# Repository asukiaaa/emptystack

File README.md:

# EmptyStack
A kicad project of empty stacking board.

In combination with [ESP32Stack](https://github.com/asukiaaa/esp32stack).

# License
MIT

# References
- [ESP32Stack](https://github.com/asukiaaa/esp32stack)

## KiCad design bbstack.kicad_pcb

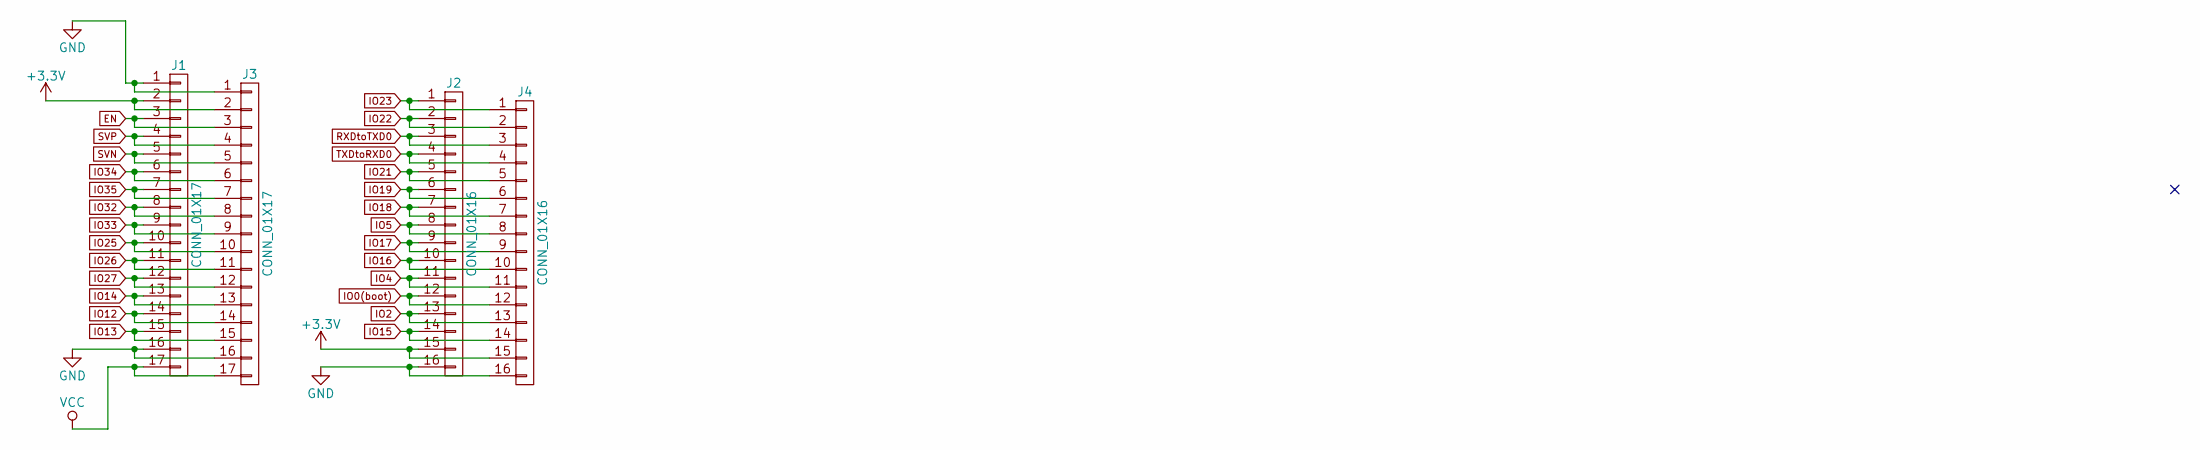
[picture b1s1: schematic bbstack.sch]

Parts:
J1, J3: CONN_01X17; Pin_Header_Straight_1x17_Pitch2.54mm
J2, J4: CONN_01X16; Pin_Header_Straight_1x16_Pitch2.54mm

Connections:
+3V3: J1.2, J2.15, J3.2, J4.15
EN: J1.3, J3.3
GND: J1.1, J1.16, J2.16, J3.1, J3.16, J4.16
IO0(boot): J2.12, J4.12
IO2: J2.13, J4.13
IO4: J2.11, J4.11
IO5: J2.8, J4.8
IO12: J1.14, J3.14
IO13: J1.15, J3.15
IO14: J1.13, J3.13
IO15: J2.14, J4.14
IO16: J2.10, J4.10
IO17: J2.9, J4.9
IO18: J2.7, J4.7
IO19: J2.6, J4.6
IO21: J2.5, J4.5
IO22: J2.2, J4.2
IO23: J2.1, J4.1
IO25: J1.10, J3.10
IO26: J1.11, J3.11
IO27: J1.12, J3.12
IO32: J1.8, J3.8
IO33: J1.9, J3.9
IO34: J1.6, J3.6
IO35: J1.7, J3.7
RXDtoTXD0: J2.3, J4.3
SVN: J1.5, J3.5
SVP: J1.4, J3.4
TXDtoRXD0: J2.4, J4.4
VCC: J1.17, J3.17

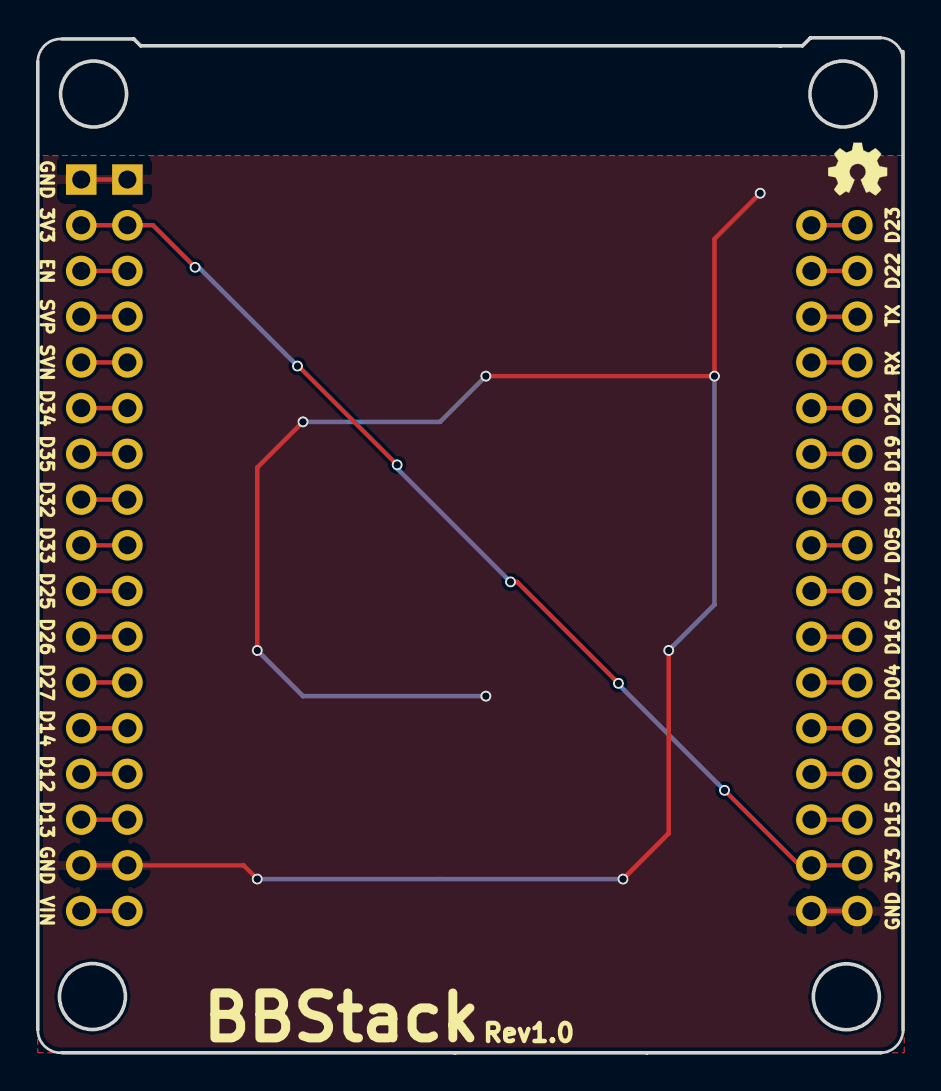
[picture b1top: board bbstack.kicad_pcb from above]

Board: 2 copper layers, 48.1 x 56.4 mm, 4 parts (0 on the bottom side), 30 nets.

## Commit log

2017-04-20 Initial commit bbstack rev1.0
2017-04-29 Add images
2017-05-01 Change file names to emptystack
2017-05-06 Add component info
